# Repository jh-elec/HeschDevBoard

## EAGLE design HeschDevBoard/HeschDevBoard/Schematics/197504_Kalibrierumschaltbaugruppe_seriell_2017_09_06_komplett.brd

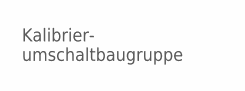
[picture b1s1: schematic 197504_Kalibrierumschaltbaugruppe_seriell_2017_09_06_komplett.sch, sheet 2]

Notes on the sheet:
Kalibrier- umschaltbaugruppe

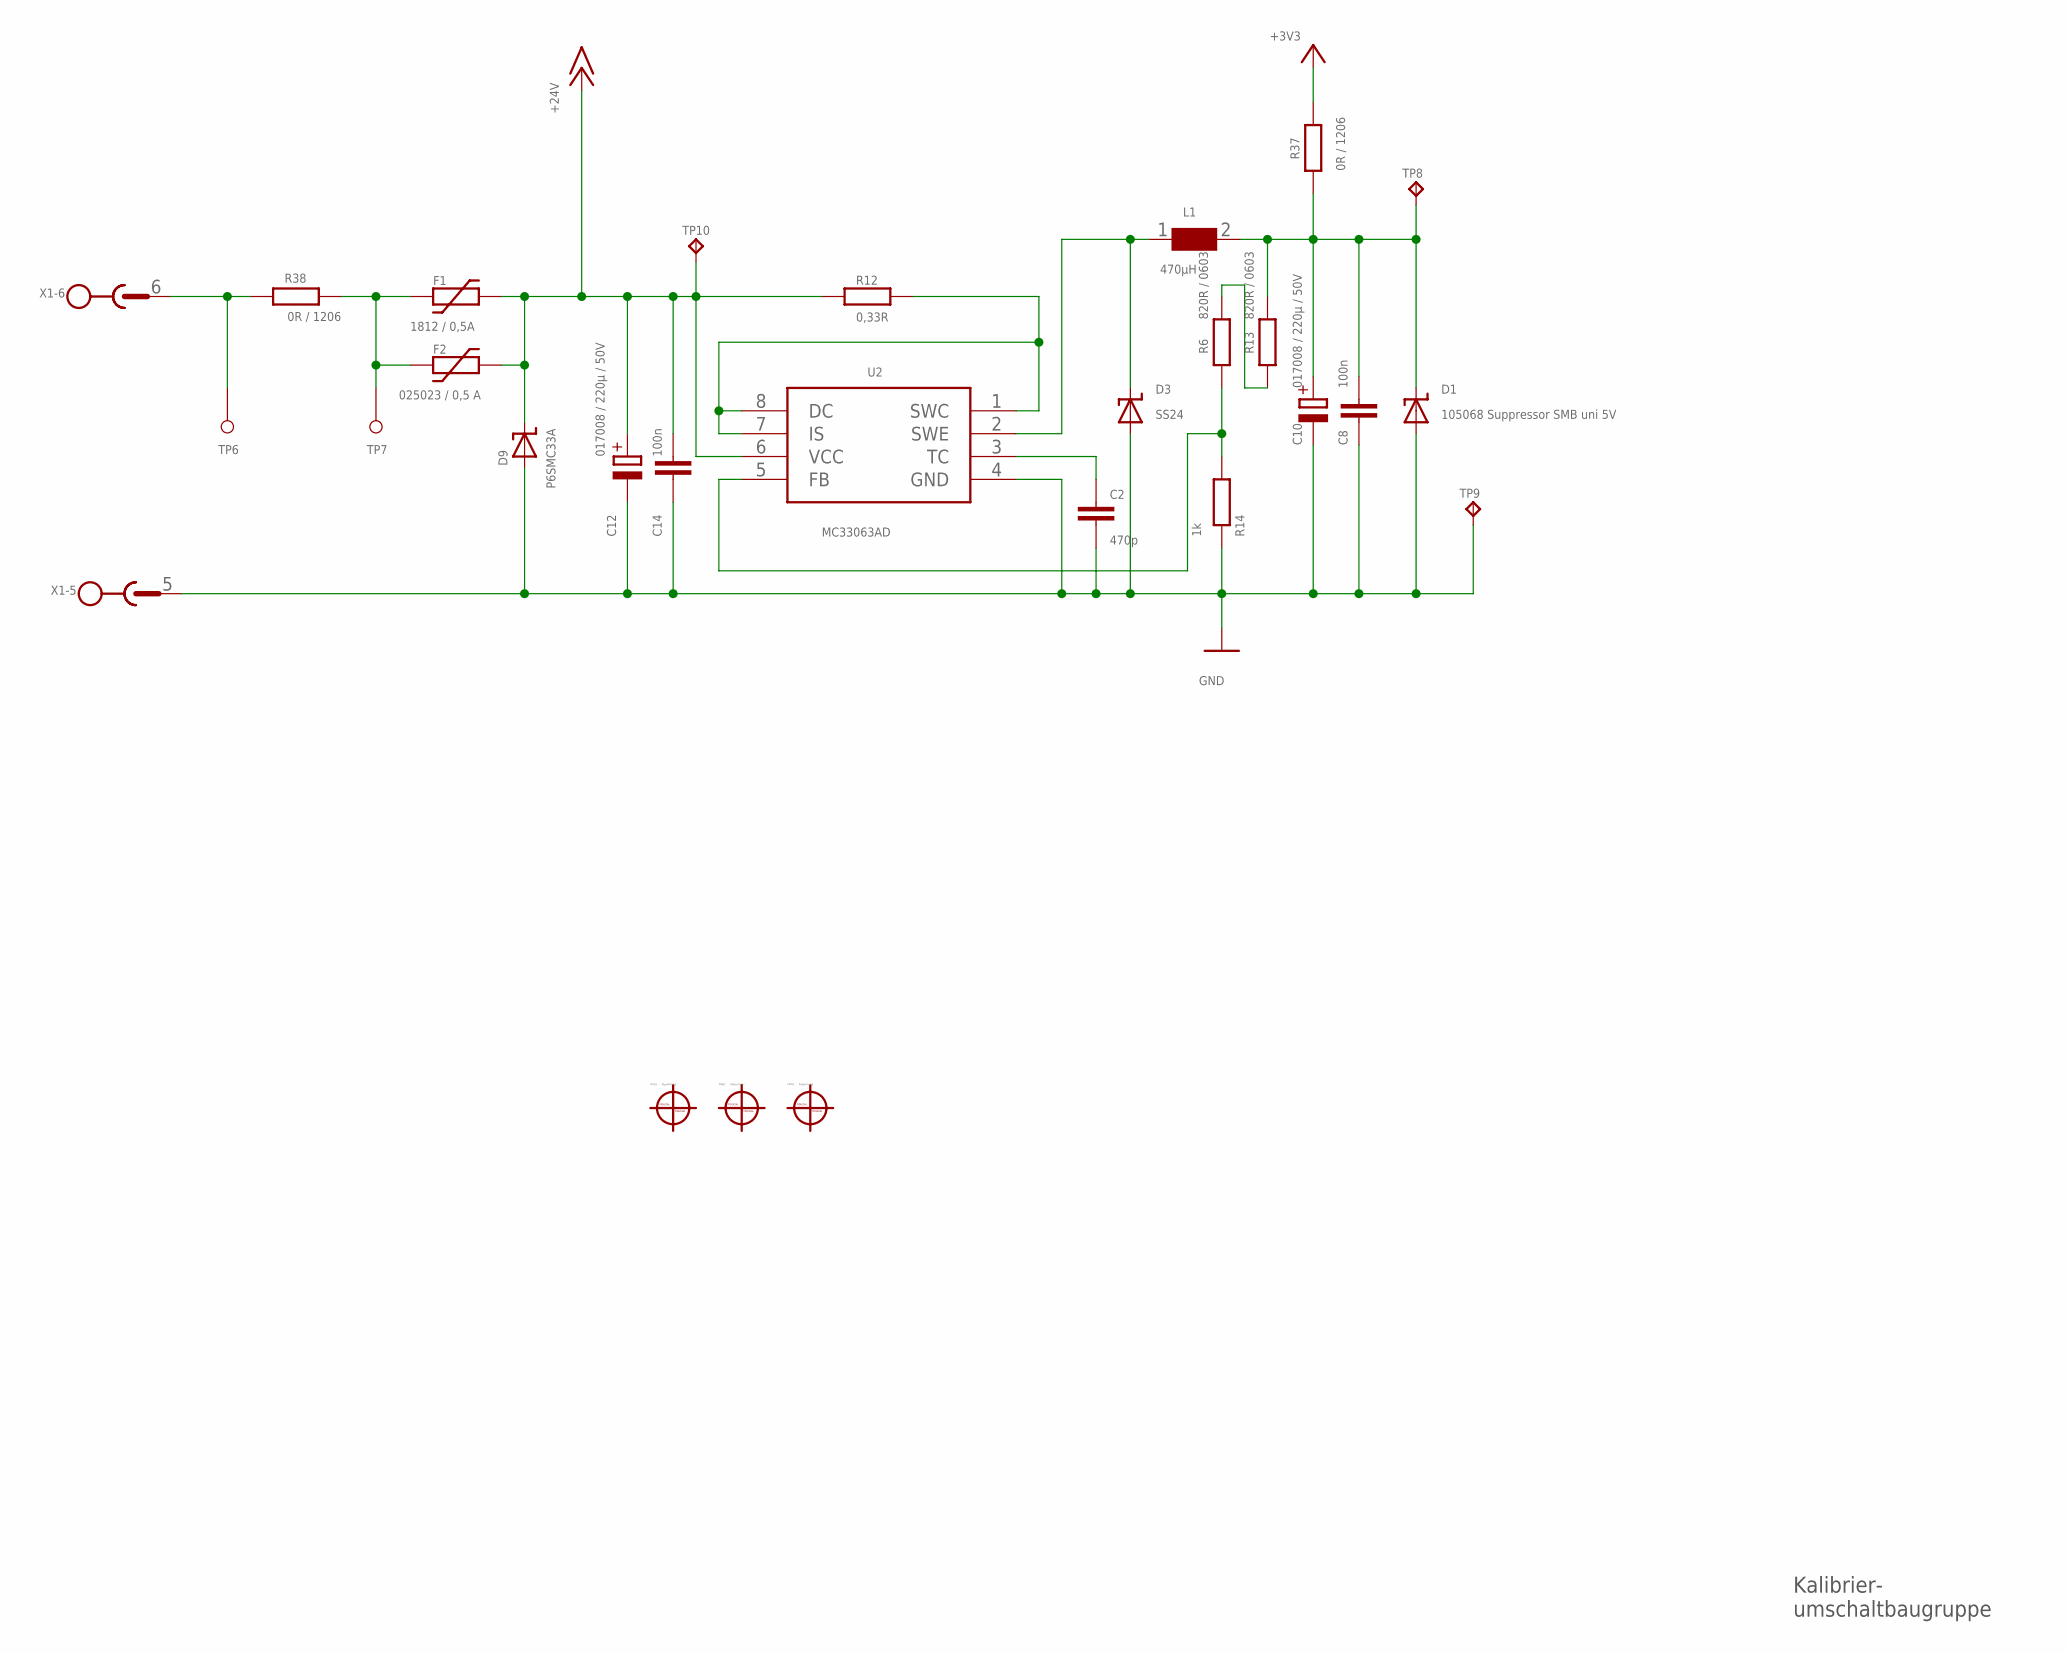
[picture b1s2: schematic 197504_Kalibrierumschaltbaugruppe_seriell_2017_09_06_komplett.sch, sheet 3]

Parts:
C2: 470p; C0603
C8, C14: 100n; C0603
C10, C12: 017008 / 220µ / 50V; 153CLV-1014
D1: 105068 Suppressor SMB uni 5V; SMBJ
D3: SS24; SMBJ
D9: P6SMC33A; SMC
F1: 1812 / 0,5A; 1812L
F2: 025023 / 0,5 A; 1206L
FIDU1, FIDU2, FIDU3: Passermarke; PASSER_1MM
L1: 470µH; L
R6, R13: 820R / 0603; R0603
R12: 0,33R; R1206
R14: 1k; R0603
R37, R38: 0R / 1206; R1206
TP6, TP7: Testpunkt_mit_Bohrung; THT-1X2,54
TP8, TP9, TP10: TPB2,54; B2,54
U2: MC33063AD; SOIC8
X1: MSTB 2,5/6-GF-5,08 AU ( Phoenix: 1949364 ); MSTB6_GF

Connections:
3V3_STABILIZED_OUT: C8.1, C10.+, D1.C, L1.2, R13.2, R37.1, TP8.PP
+3V3: R37.2; also elsewhere on the board
+24V: C12.+, C14.1, D9.C, F1.2, F2.2, R12.2, TP10.PP, U2.6 (VCC)
GND: C2.2, C8.2, C10.-, C12.-, C14.2, D1.A, D3.A, D9.A, R14.1, TP9.PP, U2.4 (GND), X1.5; also elsewhere on the board
unnamed: F1.1, F2.1, R38.1, TP7.TP
unnamed: R12.1, U2.1 (SWC), U2.7 (IS), U2.8 (DC)
unnamed: R6.2, R13.1
unnamed: D3.C, L1.1, U2.2 (SWE)
unnamed: R6.1, R14.2, U2.5 (FB)
unnamed: R38.2, TP6.TP, X1.6
unnamed: C2.1, U2.3 (TC)

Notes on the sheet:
Kalibrier- umschaltbaugruppe

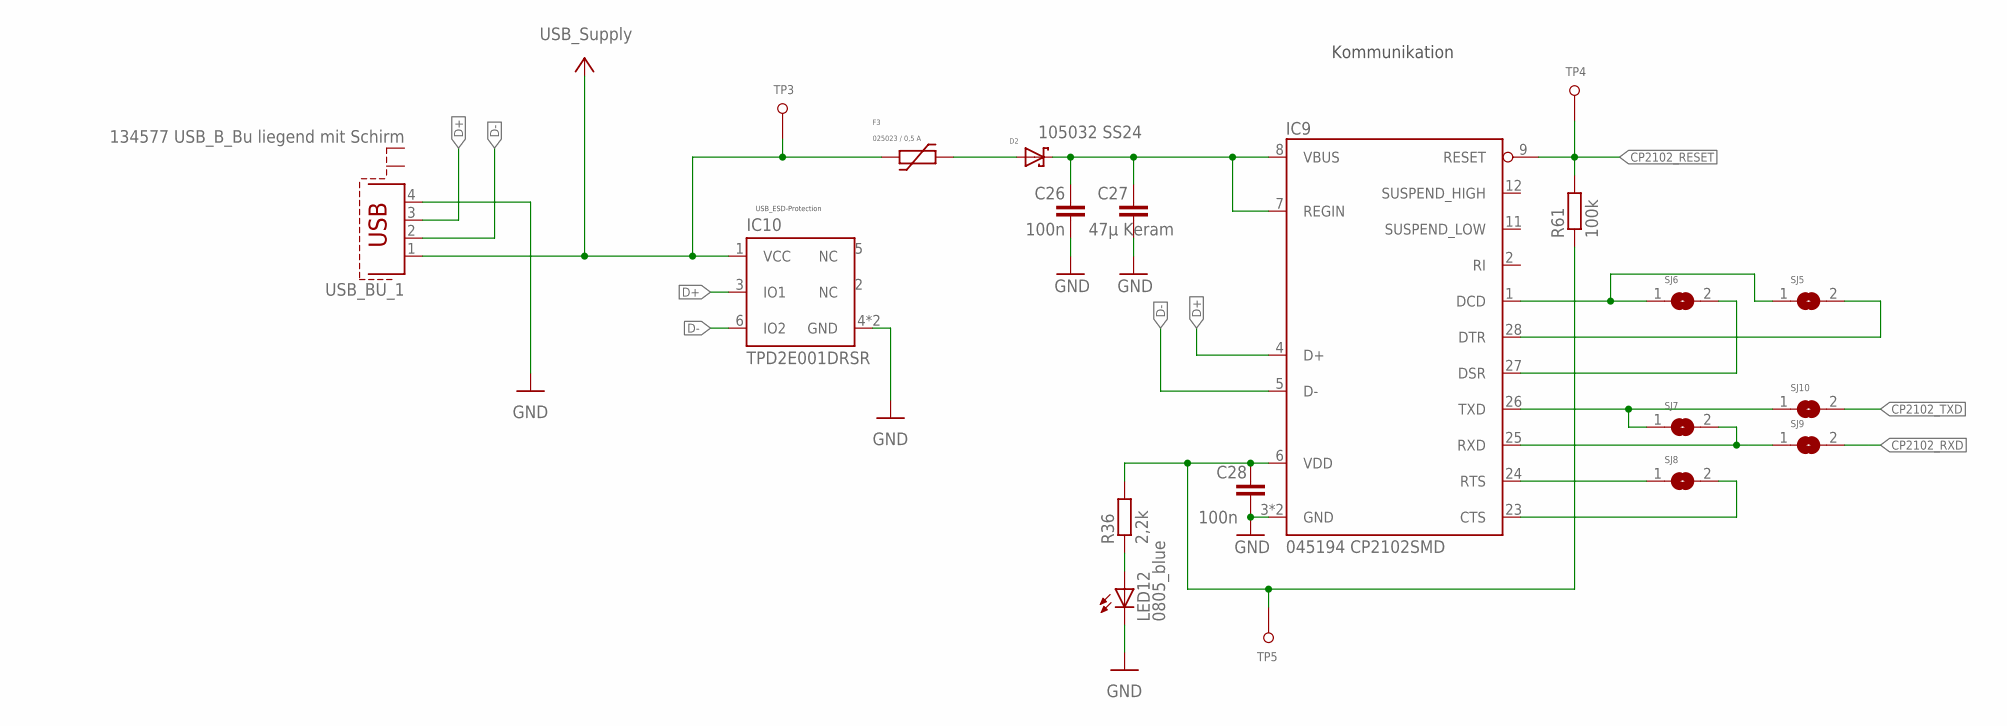
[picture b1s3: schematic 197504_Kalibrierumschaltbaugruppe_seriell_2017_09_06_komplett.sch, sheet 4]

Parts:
C26, C28: 100n; C0603
C27: 47µ Keram; C1210
D2: 105032 SS24; DO-214AA/SMB
F3: 025023 / 0,5 A; 1206L
IC9: 045194 CP2102SMD; QFN28
IC10: TPD2E001DRSR; DRS
LED12: 0805_blue; CHIPLED_0805
R36: 2,2k; R0603
R61: 100k; R0603
SJ5, SJ6, SJ7, SJ8, SJ9, SJ10: Lötjumper; SJ
TP3, TP4, TP5: Testpunkt_mit_Bohrung; THT-1X2,54
USB_BU_1: 134577 USB_B_Bu liegend mit Schirm; PN61729-S

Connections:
CP2102_RESET: IC9.9 (RESET), R61.2, TP4.TP
CP2102_RXD: SJ9.2; also elsewhere on the board
CP2102_RXD_: IC9.26 (TXD), SJ7.1, SJ10.1
CP2102_TXD: SJ10.2; also elsewhere on the board
CP2102_TXD_: IC9.25 (RXD), SJ7.2, SJ9.1
CTS: IC9.23 (CTS), SJ8.2
D+: IC9.4 (D+), IC10.3 (IO1), USB_BU_1.3
D-: IC9.5 (D-), IC10.6 (IO2), USB_BU_1.2
DCD: IC9.1 (DCD), SJ5.1, SJ6.1
DSR: IC9.27 (DSR), SJ6.2
DTR: IC9.28 (DTR), SJ5.2
GND: C26.2, C27.2, C28.2, IC9.3 (GND), IC9.THERMAL (GND), IC10.4 (GND), IC10.THERMAL (GND), LED12.C, USB_BU_1.4; also elsewhere on the board
unnamed: LED12.A, R36.1
unnamed: D2.A, F3.2
RTS: IC9.24 (RTS), SJ8.1
USB_REG_OUT: C28.1, IC9.6 (VDD), R36.2, R61.1, TP5.TP
USB_SUPPLY: F3.1, IC10.1 (VCC), TP3.TP, USB_BU_1.1
VBUS_REGIN1: C26.1, C27.1, D2.C, IC9.7 (REGIN), IC9.8 (VBUS)

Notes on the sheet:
Kommunikation
USB_ESD-Protection
